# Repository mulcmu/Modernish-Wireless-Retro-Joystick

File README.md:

# Modernish-Wireless-Retro-Joystick
 Wii Remote & ESP32 based wireless joystick interface for Atari-style joysticks.

## Goals & Objectives:

- Support for 2 Atari style joystick DB-9 connections.  Directions, Trigger, and two analog (variable resistance) values.
- Use Wiimote, Nunchuk , gamepad for input devices.  Configurable input setup options to accommodate different homebrew hardware.  (Like Wiimote tilt sensor used like paddle controller rotation.)
- Increase distance of busy little hands from vintage hardware.

## Current Status:

See build log on [hackaday.io](https://hackaday.io/project/179786-modernish-wireless-retro-joystick)

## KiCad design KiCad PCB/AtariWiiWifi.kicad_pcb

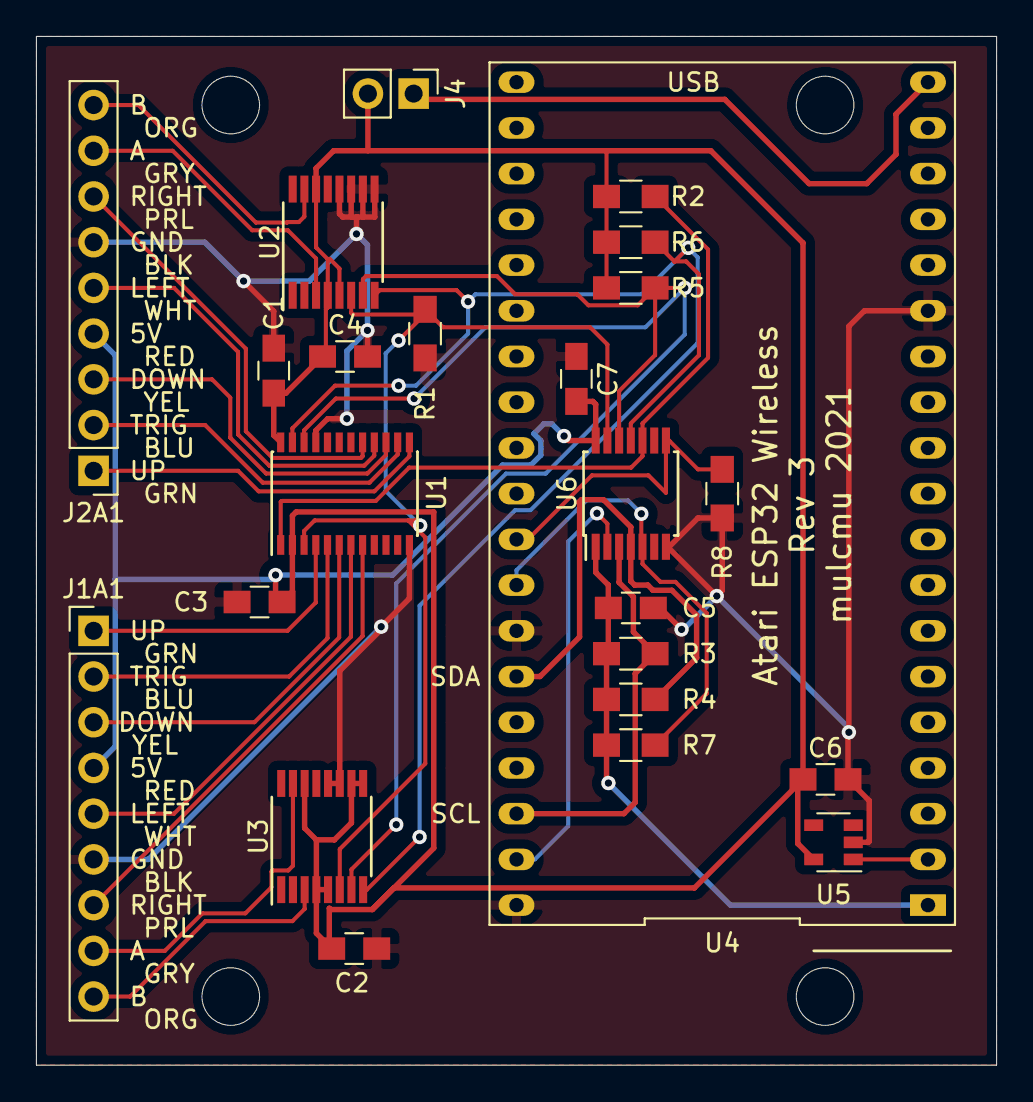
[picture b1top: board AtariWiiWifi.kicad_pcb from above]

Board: 2 copper layers, 53.3 x 57.1 mm, 24 parts (0 on the bottom side), 28 nets.

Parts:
C1, C2, C3, C4, C5, C6, C7: C; C_0805_HandSoldering
J1A1, J2A1: Conn_01x09; Pin_Header_Straight_1x09_Pitch2.54mm
J4: Conn_01x02_Male; Pin_Header_Straight_1x02_Pitch2.54mm
R1, R2, R3, R4, R5, R6, R7, R8: R; R_0805_HandSoldering
U1: PCAL6416APW; TSSOP-24_4.4x7.8mm_Pitch0.65mm
U2, U3: AD5242; TSSOP-16_4.4x5mm_Pitch0.65mm
U4: ESP32; DIP-38_900_ELL
U5: MIC2775; SOT-23-5
U6: TXS0104E; TSSOP-14_4.4x5mm_Pitch0.65mm

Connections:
+3V3: C5.1, R3.1, R4.1, R7.1, U4.1, U6.1
+5V: C1.1, C2.1, C3.1, C4.1, C6.1, C7.1, J1A1.4, J2A1.4, J4.2, R2.1, R5.2, R6.1, U1.2, U1.24, U2.4, U2.5, U2.14, U3.4, U3.5, U3.9, U3.10, U3.14, U5.5, U6.14
/INT: R7.2, U4.31, U6.5
/INT_5: R2.2, U1.1, U6.10
/J1_DOWN: J1A1.3, U1.6
/J1_LEFT: J1A1.5, U1.7
/J1_PotA: J1A1.8, U3.15
/J1_PotB: J1A1.9, U3.3
/J1_RIGHT: J1A1.7, U1.8
/J1_TRIG: J1A1.2, U1.5
/J1_UP: J1A1.1, U1.4
/J2_DOWN: J2A1.3, U1.15
/J2_LEFT: J2A1.5, U1.16
/J2_PotA: J2A1.8, U2.3
/J2_PotB: J2A1.9, U2.15
/J2_RIGHT: J2A1.7, U1.17
/J2_TRIG: J2A1.2, U1.14
/J2_UP: J2A1.1, U1.13
/READY: R1.1, U1.3, U2.6, U3.6, U6.13
/SCL: R3.2, U4.36, U6.3
/SDA: R4.2, U4.33, U6.4
/SDA_5: R5.1, U1.23, U2.8, U3.8, U6.11
/SLC_5: R6.2, U1.22, U2.7, U3.7, U6.12
GND: C1.2, C2.2, C3.2, C4.2, C5.2, C6.2, C7.2, J1A1.6, J2A1.6, R1.2, R8.2, U1.12, U1.21, U2.9, U2.10, U2.11, U2.12, U3.11, U3.12, U4.14, U4.32, U4.38, U5.2, U6.7
unnamed: J4.1, U4.19
unnamed: R8.1, U4.30, U6.8
unnamed: U4.2, U5.1
unnamed: U4.37, U6.2

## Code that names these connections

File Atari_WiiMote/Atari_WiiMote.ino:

#include <Wire.h> //include Wire.h library
#include <esp_types.h>

#include "ESP32Wiimote.h"
ESP32Wiimote wiimote;


#include <atomic>
using namespace std;

//i2c addresses
#define AD5242_J1_ADDRESS 0x2F
#define AD5242_J2_ADDRESS 0x2C
#define PCAL6416A_ADDRESS 0x20

//i2c commands/registers
#define AS524X_RDAC0         0x00
#define AS524X_RDAC1         0x80
#define PCAL6416A_OUTPUT_CFG 0x4F
#define PCAL6416A_DIRECTION  0x06
#define PCAL6416A_OUTPUT     0x02

byte error=0;
uint8_t i=0;
unsigned long t=0;

std::atomic<std::uint8_t> J1_btn;
std::atomic<std::uint8_t> J1_PotA;
std::atomic<std::uint8_t> J1_PotB;

std::atomic<std::uint8_t> J2_btn;
std::atomic<std::uint8_t> J2_PotA;
std::atomic<std::uint8_t> J2_PotB;


TaskHandle_t i2c_taskHandle;


//WiiMote buttons defined for vertical orientation
//Add  _H_ for horizonal orientation
#define BUTTON_H_DOWN     BUTTON_LEFT
#define BUTTON_H_UP       BUTTON_RIGHT
#define BUTTON_H_LEFT     BUTTON_UP
#define BUTTON_H_RIGHT    BUTTON_DOWN

//PCAL6416A button mapping
#define PCAL6416A_UP     0b00000001
#define PCAL6416A_DOWN   0b00000100
#define PCAL6416A_LEFT   0b00001000
#define PCAL6416A_RIGHT  0b00010000
#define PCAL6416A_TRIGR  0b00000010

void setup()
{
 J1_btn=0;
 J1_PotA=0;
 J1_PotB=0;
 J2_btn=0;
 J2_PotA=0;
 J2_PotB=0;

 
  //power up delay.
  delay(250);
  
  Wire.begin(); // Wire communication begin
  
  Serial.begin(115200); 
  //while (!Serial); // Waiting for Serial Monitor

  Serial.println("Atari WiiMote test code.");
  
  //Configure outputs as open-drain (default is push-pull)
  Wire.beginTransmission(PCAL6416A_ADDRESS);
  Wire.write(PCAL6416A_OUTPUT_CFG); 
  Wire.write(0b00000011);
  Wire.endTransmission();

  delay(100);

  //Configure P0.0 to P0.4 and P1.0 to P1.4 as outputs
  Wire.beginTransmission(PCAL6416A_ADDRESS);
  Wire.write(PCAL6416A_DIRECTION); 
  Wire.write(0b11100000);  //Port 0:  1 input, 0 output
  Wire.write(0b11100000);  //Port 1:  
  Wire.endTransmission();
  
  //create a task that will process i2c on core 0
  xTaskCreatePinnedToCore(
                    i2c_loop,       /* Task function. */
                    "i2c Loop",     /* name of task. */
                    10000,          /* Stack size of task */
                    NULL,            /* parameter of the task */
                    1,              /* priority of the task */
                    &i2c_taskHandle,/* Task handle to keep track of created task */
                    0);             /* pin task to core 0 */

    wiimote.init();
    //wiimote.addFilter(ACTION_IGNORE, FILTER_ACCEL); // optional
 
}

//Standard loop handles wiiMote on Core 1
void loop()
{
    wiimote.task();
  if (wiimote.available() > 0) 
    {
      ButtonState  button  = wiimote.getButtonState();
      
      (button & BUTTON_H_UP)    ?    J1_btn |= PCAL6416A_UP     :  J1_btn &= ~PCAL6416A_UP;
      (button & BUTTON_H_DOWN)  ?    J1_btn |= PCAL6416A_DOWN   :  J1_btn &= ~PCAL6416A_DOWN;
      (button & BUTTON_H_LEFT)  ?    J1_btn |= PCAL6416A_LEFT   :  J1_btn &= ~PCAL6416A_LEFT;
      (button & BUTTON_H_RIGHT) ?    J1_btn |= PCAL6416A_RIGHT  :  J1_btn &= ~PCAL6416A_RIGHT;
      (button & BUTTON_TWO)     ?    J1_btn |= PCAL6416A_TRIGR  :  J1_btn &= ~PCAL6416A_TRIGR;
      
      J2_btn.store(J1_btn.load());

      

      if (button & BUTTON_HOME) {
        J1_PotA = 128;
        J1_PotB = 128;
        J2_PotA = 128;
        J2_PotB = 128;
      }

      if (J1_PotA < 253 && button & BUTTON_PLUS) {
        J1_PotA++;
        J1_PotB++;
        J2_PotA++;
        J2_PotB++;
      }

      if (J1_PotA > 3 && button & BUTTON_MINUS){
        J1_PotA--;
        J1_PotB--;
        J2_PotA--;
        J2_PotB--;
      }

    Serial.println(J1_btn);
    Serial.println(J1_PotA);

      
    }

}



void wiiMote_Debug(void)  {
  if (wiimote.available() > 0) 
    {
        ButtonState  button  = wiimote.getButtonState();
        AccelState   accel   = wiimote.getAccelState();
        NunchukState nunchuk = wiimote.getNunchukState();

        if (1)
        {
            char ca     = (button & BUTTON_A)     ? 'A' : '.';
            char cb     = (button & BUTTON_B)     ? 'B' : '.';
            char cc     = (button & BUTTON_C)     ? 'C' : '.';
            char cz     = (button & BUTTON_Z)     ? 'Z' : '.';
            char c1     = (button & BUTTON_ONE)   ? '1' : '.';
            char c2     = (button & BUTTON_TWO)   ? '2' : '.';
            char cminus = (button & BUTTON_MINUS) ? '-' : '.';
            char cplus  = (button & BUTTON_PLUS)  ? '+' : '.';
            char chome  = (button & BUTTON_HOME)  ? 'H' : '.';
            char cleft  = (button & BUTTON_LEFT)  ? '<' : '.';
            char cright = (button & BUTTON_RIGHT) ? '>' : '.';
            char cup    = (button & BUTTON_UP)    ? '^' : '.';
            char cdown  = (button & BUTTON_DOWN)  ? 'v' : '.';
      
            Serial.printf("button: %05x = ", (int)button);
            Serial.print(ca);
            Serial.print(cb);
            Serial.print(cc);
            Serial.print(cz);
            Serial.print(c1);
            Serial.print(c2);
            Serial.print(cminus);
            Serial.print(chome);
            Serial.print(cplus);
            Serial.print(cleft);
            Serial.print(cright);
            Serial.print(cup);
            Serial.print(cdown);
            Serial.printf(", wiimote.axis: %3d/%3d/%3d", accel.xAxis, accel.yAxis, accel.zAxis);
            Serial.printf(", nunchuk.axis: %3d/%3d/%3d", nunchuk.xAxis, nunchuk.yAxis, nunchuk.zAxis);
            Serial.printf(", nunchuk.stick: %3d/%3d\n", nunchuk.xStick, nunchuk.yStick);
        }
    }
}




//i2c loop runs on core 0
void i2c_loop( void * pvParameters ){
  //Serial.print("i2c running on core ");
  //Serial.println(xPortGetCoreID());

  for(;;){
    Wire.beginTransmission(AD5242_J1_ADDRESS);
    Wire.write(AS524X_RDAC0);
    Wire.write(J1_PotA);
    Wire.endTransmission();
    
    Wire.beginTransmission(AD5242_J1_ADDRESS);
    Wire.write(AS524X_RDAC1);
    Wire.write(J1_PotB);
    Wire.endTransmission();

      
    Wire.beginTransmission(AD5242_J2_ADDRESS);
    Wire.write(AS524X_RDAC0);
    Wire.write(J2_PotA);
    Wire.endTransmission();

    
    Wire.beginTransmission(AD5242_J2_ADDRESS);
    Wire.write(AS524X_RDAC1);
    Wire.write(J2_PotB);
    Wire.endTransmission();

    Wire.beginTransmission(PCAL6416A_ADDRESS);
    Wire.write(PCAL6416A_OUTPUT); //Output Register
    Wire.write(~J1_btn);  //Port 0
    Wire.write(~J2_btn);  //Port 1  
    Wire.endTransmission();

  }
}

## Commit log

2021-05-15 Rev1 PCB
2021-05-20 Update README.md
    typo
2021-06-06 Add i2c_test Ardunio Code
    Add test code used to test basic board operation.
2021-06-09 Update PCB to Rev 2
    Fixed Digital pots connected to ground instead of +5.
    Added jumper to power ESP from Atari
2021-06-14 Create Atari_WiiMote.ino
    Working demo code for single WiiMote joystick. Still troubleshooting the pot
2021-06-18 Update Schematic.pdf
    Rev 2.1 testing for i2c level shifting
2021-06-23 Update Schematic.pdf
    Rev 3
2021-06-26 Rev 3 PCB
    Update Rev 3 PCB files.
    Small Tweak to Schematic for extra bypass cap.
